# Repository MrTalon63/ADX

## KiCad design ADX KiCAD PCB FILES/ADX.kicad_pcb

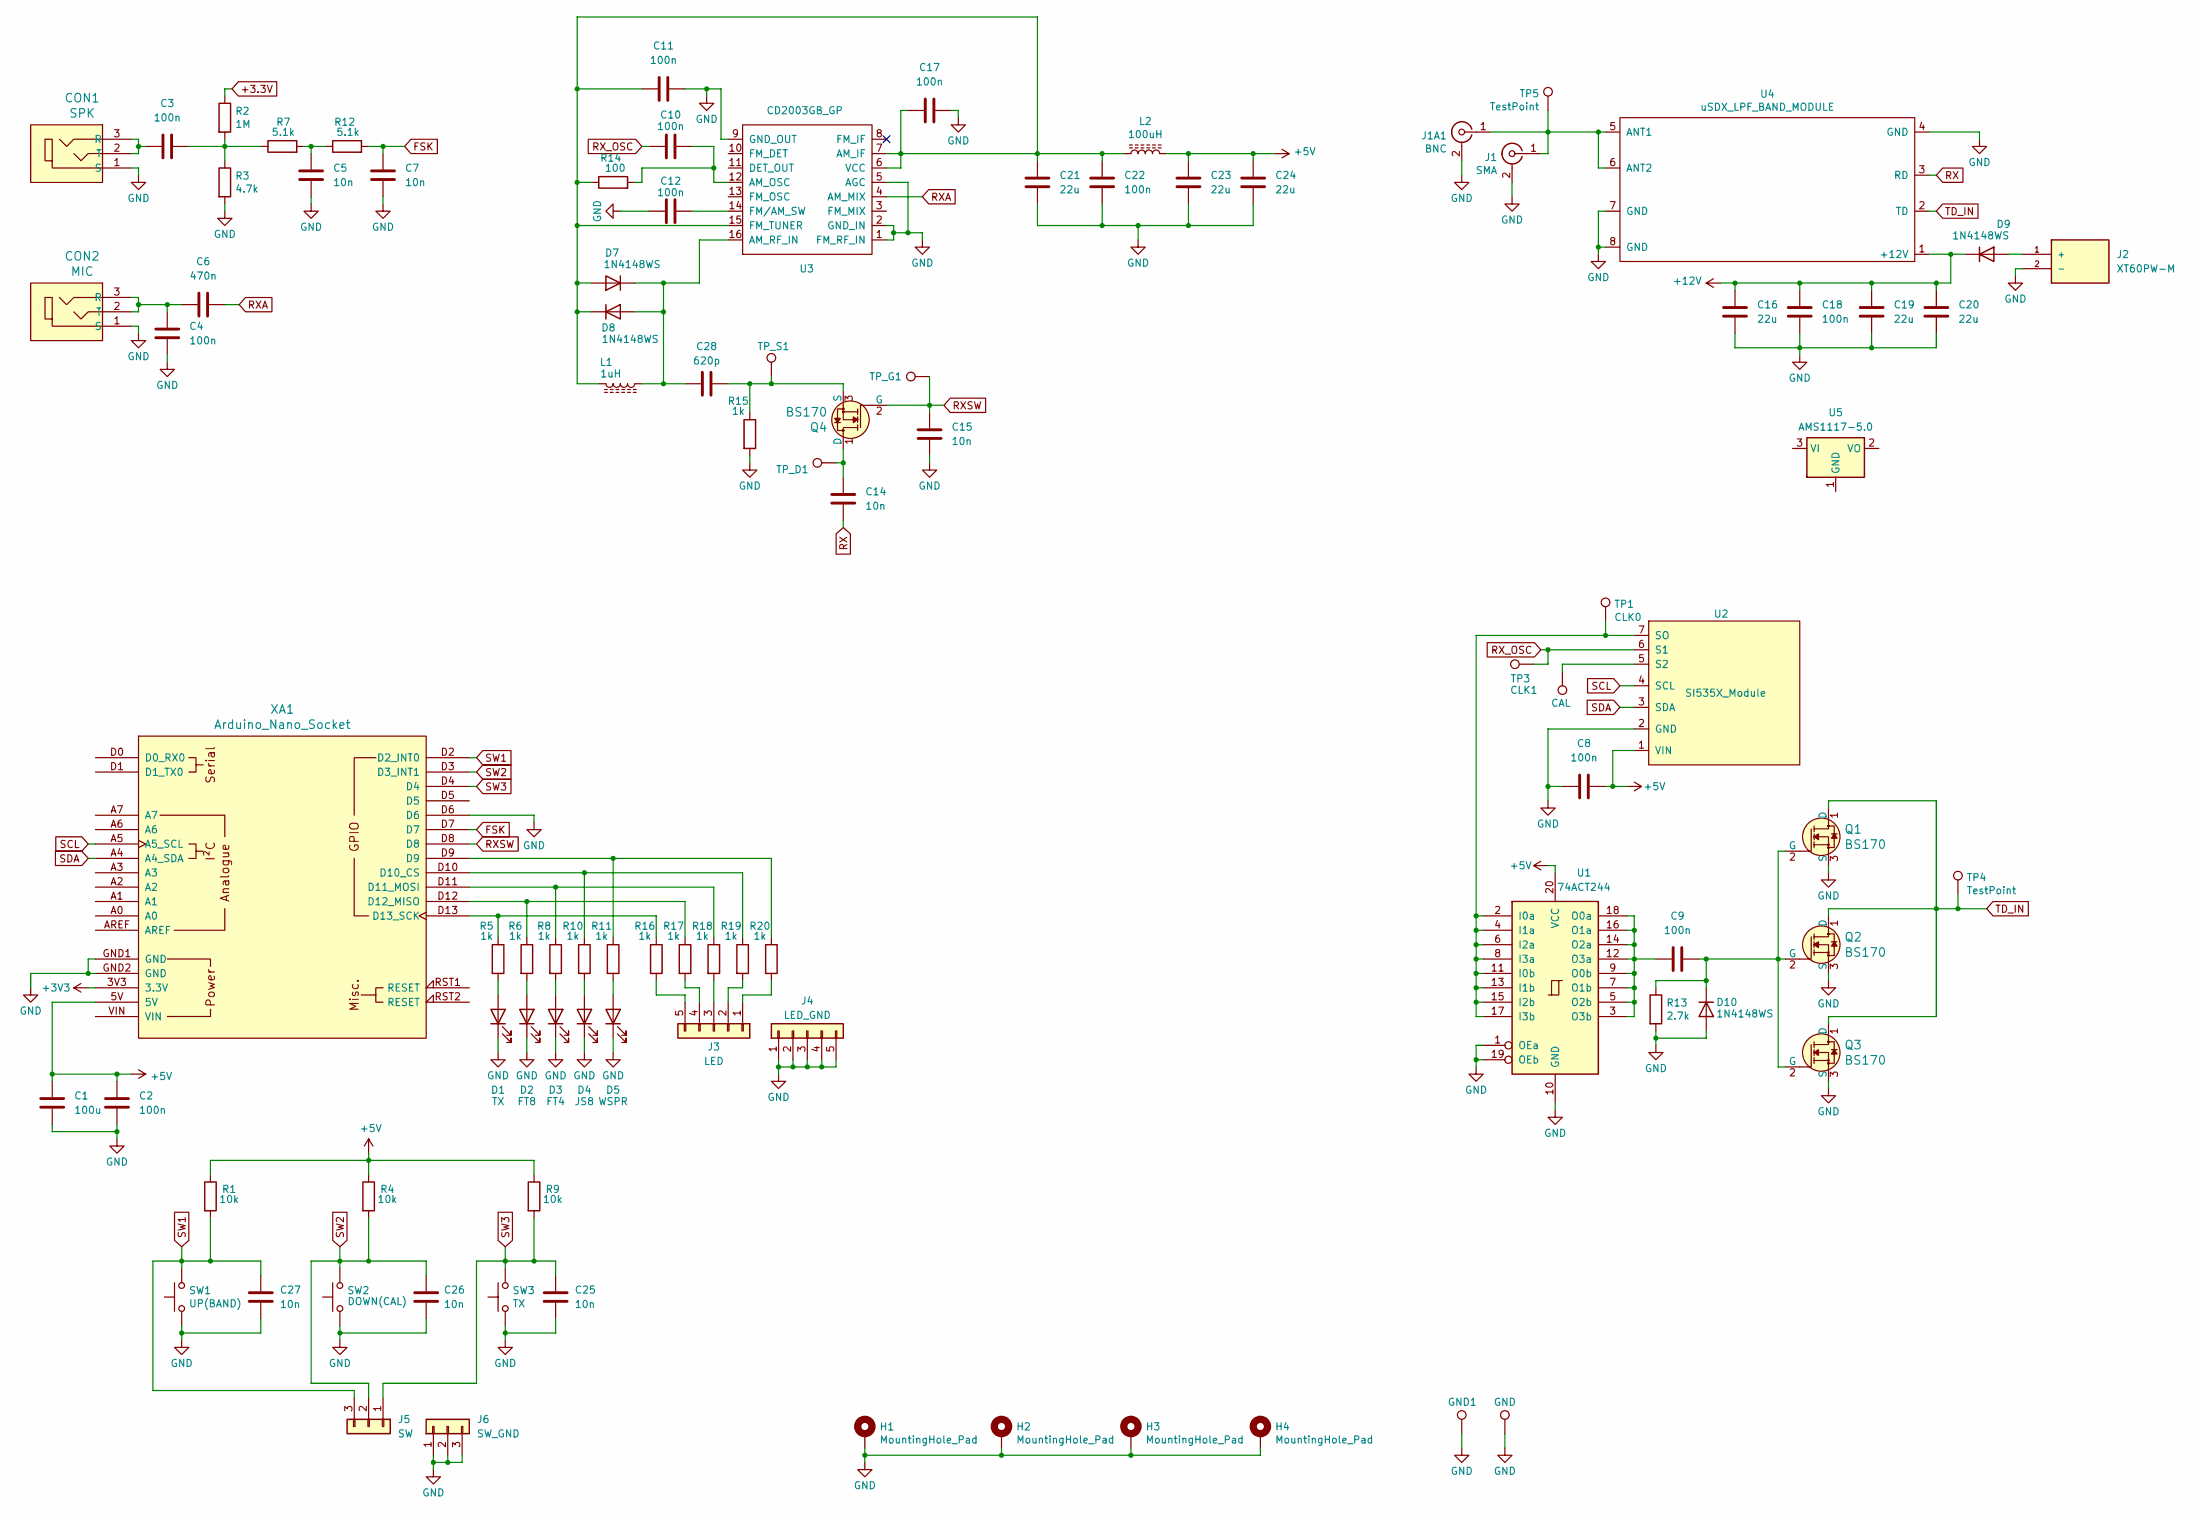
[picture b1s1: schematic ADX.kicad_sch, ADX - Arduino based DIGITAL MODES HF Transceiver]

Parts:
C1: 100u; C_1206_3216Metric
C2, C3, C4, C8, C9, C10, C11, C12, C17, C18, C22: 100n; C_0805_2012Metric
C5, C7, C14, C15, C25, C26, C27: 10n; C_0805_2012Metric
C6: 470n; C_0603_1608Metric
C16, C19, C20, C21, C23, C24: 22u; C_0805_2012Metric
C28: 620p; C_0805_2012Metric
CON1: SPK; Headphone_Jack_3.5mm_SJ1-3523N; MPN SJ1-3523N; Digi-Key_PN CP1-3523N-ND
CON2: MIC; Headphone_Jack_3.5mm_SJ1-3523N; MPN SJ1-3523N; Digi-Key_PN CP1-3523N-ND
D1: TX; LED_D3.0mm
D2: FT8; LED_D3.0mm
D3: FT4; LED_D3.0mm
D4: JS8; LED_D3.0mm
D5: WSPR; LED_D3.0mm
D7, D8, D9, D10: 1N4148WS; D_SOD-323
GND1: TestPoint_THTPad_2.0x2.0mm_Drill1.0mm
H1, H2, H3, H4: MountingHole_Pad; MountingHole_3.2mm_M3_ISO7380_Pad
J1: SMA; SMA_Samtec_SMA-J-P-X-ST-EM1_EdgeMount
J1A1: BNC; BNC_Amphenol_B6252HB-NPP3G-50_Horizontal
J2: XT60PW-M; AMASS_XT60PW-M; PARTREV V1.2
J3: LED; PinHeader_1x05_P2.54mm_Vertical
J4: LED_GND; PinHeader_1x05_P2.54mm_Vertical
J5: SW; PinHeader_1x03_P2.54mm_Vertical
J6: SW_GND; PinHeader_1x03_P2.54mm_Vertical
L1: 1uH; L_0805_2012Metric_Pad1.05x1.20mm_HandSolder
L2: 100uH; R_Axial_DIN0204_L3.6mm_D1.6mm_P2.54mm_Vertical
Q1, Q2, Q3: BS170; TO-92_HandSolder; MPN BS170; Digi-Key_PN BS170-ND
Q4: BS170; TO-92L_HandSolder; MPN BS170; Digi-Key_PN BS170-ND
R1, R4, R9: 10k; R_0402_1005Metric
R2: 1M; R_0402_1005Metric
R3: 4.7k; R_0402_1005Metric
R5, R6, R8, R10, R11, R15, R16, R17, R18, R19, R20: 1k; R_0402_1005Metric
R7, R12: 5.1k; R_0402_1005Metric
R13: 2.7k; R_0603_1608Metric
R14: 100; R_0402_1005Metric
SW1: UP(BAND); SW_PUSH_6mm
SW2: DOWN(CAL); SW_PUSH_6mm
SW3: TX; SW_PUSH_6mm
TP1: CLK0; TestPoint_THTPad_2.0x2.0mm_Drill1.0mm
TP2: CAL; TestPoint_THTPad_2.0x2.0mm_Drill1.0mm
TP3: CLK1; TestPoint_THTPad_2.0x2.0mm_Drill1.0mm
TP4, TP5: TestPoint; TestPoint_THTPad_2.0x2.0mm_Drill1.0mm
TP6: GND; TestPoint_THTPad_2.0x2.0mm_Drill1.0mm
TP_D1: TestPoint_THTPad_1.0x1.0mm_Drill0.5mm
TP_G1: TestPoint_THTPad_1.0x1.0mm_Drill0.5mm
TP_S1: TestPoint_THTPad_1.0x1.0mm_Drill0.5mm
U1: 74ACT244; TSSOP-20_4.4x6.5mm_P0.65mm
U2: SI535X_Module; SI5351 Module_Vertical
U3: CD2003GB_GP; DIP-16_W7.62mm_Socket_LongPads
U4: uSDX_LPF_BAND_MODULE; uSDX_LPF_Band_Module
U5: AMS1117-5.0; SOT-223-3_TabPin2
XA1: Arduino_Nano_Socket

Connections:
+3.3V: R2.1
+3V3: XA1.3V3 (3.3V)
+5V: C1.1, C2.1, C8.2, C23.1, C24.1, L2.1, R1.1, R4.1, R9.1, U1.20 (VCC), U2.1 (VIN), XA1.5V
+12V: C16.1, C18.1, C19.1, C20.1, D9.1 (K), U4.1 (+12V)
FSK: C7.2, R12.2, XA1.D7
GND: C1.2, C2.2, C4.1, C5.1, C7.1, C8.1, C11.2, C12.1, C15.1, C16.2, C17.2, C18.2, C19.2, C20.2, C21.2, C22.2, C23.2, C24.2, C25.1, C26.1, C27.1, CON1.1 (S), CON2.1 (S), D1.1 (K), D2.1 (K), D3.1 (K), D4.1 (K), D5.1 (K), D10.2 (A), GND1.1, H1.1, H2.1, H3.1, H4.1, J1.2 (Ext), J1A1.2 (Ext), J2.2 (-), J4.1, J4.2, J4.3, J4.4, J4.5, J6.1, J6.2, J6.3, Q1.3 (S), Q2.3 (S), Q3.3 (S), R3.2, R13.2, R15.2, SW1.1, SW2.1, SW3.1, TP6.1, U1.1 (OEa), U1.10 (GND), U1.19 (OEb), U2.2 (GND), U3.1 (FM_RF_IN), U3.2 (GND_IN), U3.5 (AGC), U3.9 (GND_OUT), U4.4 (GND), U4.7 (GND), U4.8 (GND), XA1.D6, XA1.GND1 (GND), XA1.GND2 (GND)
unnamed: C3.2, R2.2, R3.1, R7.1
unnamed: C5.2, R7.2, R12.1
unnamed: C3.1, CON1.2 (T), CON1.3 (R)
unnamed: C4.2, C6.1, CON2.2 (T), CON2.3 (R)
unnamed: D1.2 (A), R5.2
unnamed: D2.2 (A), R6.2
unnamed: D3.2 (A), R8.2
unnamed: D4.2 (A), R10.2
unnamed: D5.2 (A), R11.2
unnamed: C11.1, C17.1, C21.1, C22.1, D7.2 (A), D8.1 (K), L1.2, L2.2, R14.1, U3.6 (VCC), U3.7 (AM_IF), U3.15 (FM_TUNER)
unnamed: C28.2, D7.1 (K), D8.2 (A), L1.1, U3.16 (AM_RF_IN)
unnamed: D9.2 (A), J2.1 (+)
unnamed: C9.2, D10.1 (K), Q1.2 (G), Q2.2 (G), Q3.2 (G), R13.1
unnamed: J1.1 (In), J1A1.1 (In), TP5.1, U4.5 (ANT1), U4.6 (ANT2)
unnamed 20: J3.1, R20.2; also elsewhere on the board
unnamed 21: J3.2, R19.2; also elsewhere on the board
unnamed 22: J3.3, R18.2; also elsewhere on the board
unnamed 23: J3.4, R17.2; also elsewhere on the board
unnamed 24: J3.5, R16.2; also elsewhere on the board
unnamed: C14.2, Q4.1 (D), TP_D1.1
unnamed: C28.1, Q4.3 (S), R15.1, TP_S1.1
unnamed 27: R11.1, R20.1, XA1.D9; also elsewhere on the board
unnamed: TP1.1, U1.2 (I0a), U1.4 (I1a), U1.6 (I2a), U1.8 (I3a), U1.11 (I0b), U1.13 (I1b), U1.15 (I2b), U1.17 (I3b), U2.7 (SO)
unnamed: C9.1, U1.3 (O3b), U1.5 (O2b), U1.7 (O1b), U1.9 (O0b), U1.12 (O3a), U1.14 (O2a), U1.16 (O1a), U1.18 (O0a)
unnamed: TP2.1, U2.5 (S2)
unnamed: C10.2, R14.2, U3.12 (AM_OSC)
unnamed: C12.2, U3.14 (FM/AM_SW)
unnamed 33: R10.1, R19.1, XA1.D10 (D10_CS); also elsewhere on the board
unnamed 34: R8.1, R18.1, XA1.D11 (D11_MOSI); also elsewhere on the board
unnamed 35: R6.1, R17.1, XA1.D12 (D12_MISO); also elsewhere on the board
unnamed 36: R5.1, R16.1, XA1.D13 (D13_SCK); also elsewhere on the board
RX: C14.1, U4.3 (RD)
RXA: C6.2, U3.4 (AM_MIX)
RXSW: C15.2, Q4.2 (G), TP_G1.1, XA1.D8
RX_OSC: C10.1, TP3.1, U2.6 (S1)
SCL: U2.4 (SCL), XA1.A5 (A5_SCL)
SDA: U2.3 (SDA), XA1.A4 (A4_SDA)
SW1: C27.2, J5.3, R1.2, SW1.2, XA1.D2 (D2_INT0)
SW2: C26.2, J5.2, R4.2, SW2.2, XA1.D3 (D3_INT1)
SW3: C25.2, J5.1, R9.2, SW3.2, XA1.D4
TD_IN: Q1.1 (D), Q2.1 (D), Q3.1 (D), TP4.1, U4.2 (TD)

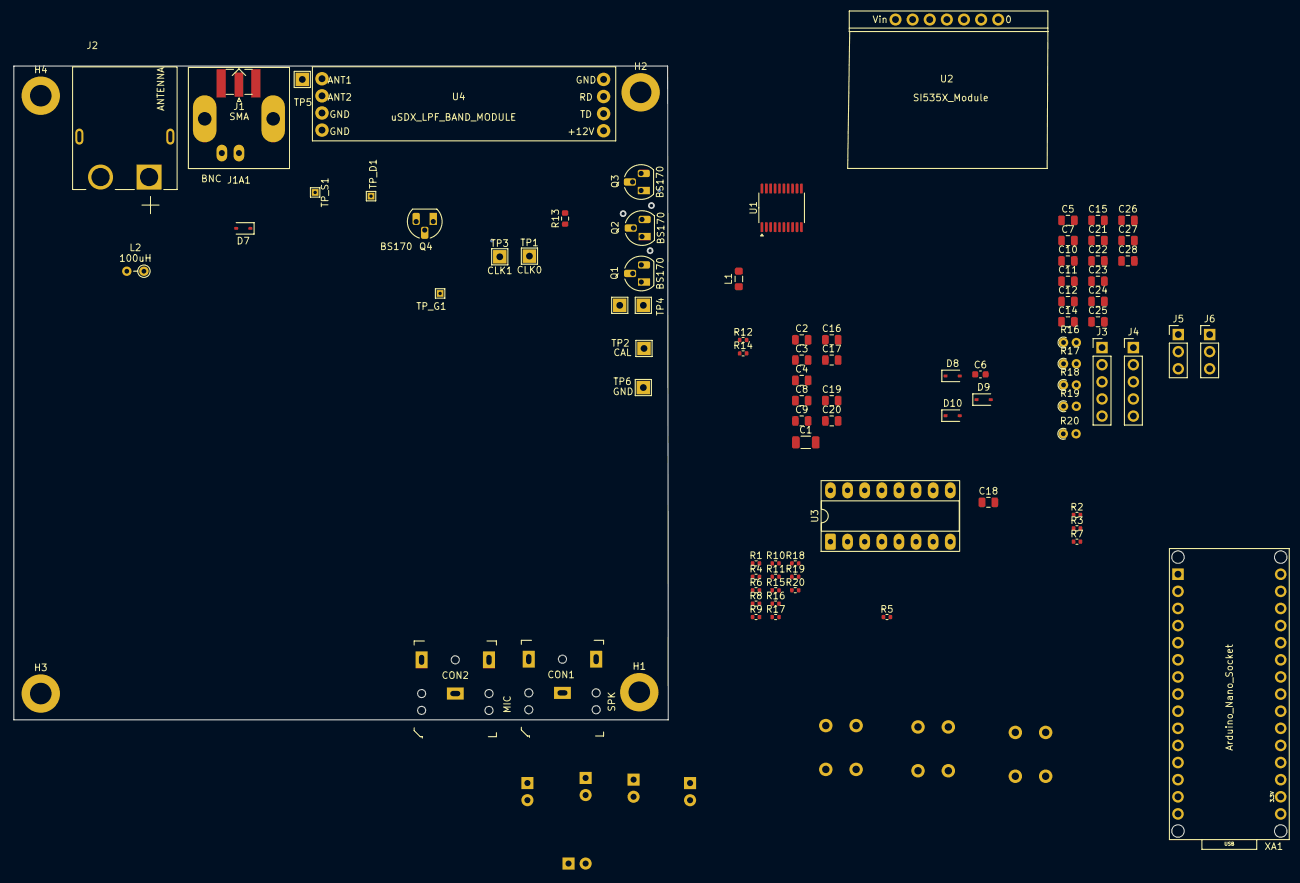
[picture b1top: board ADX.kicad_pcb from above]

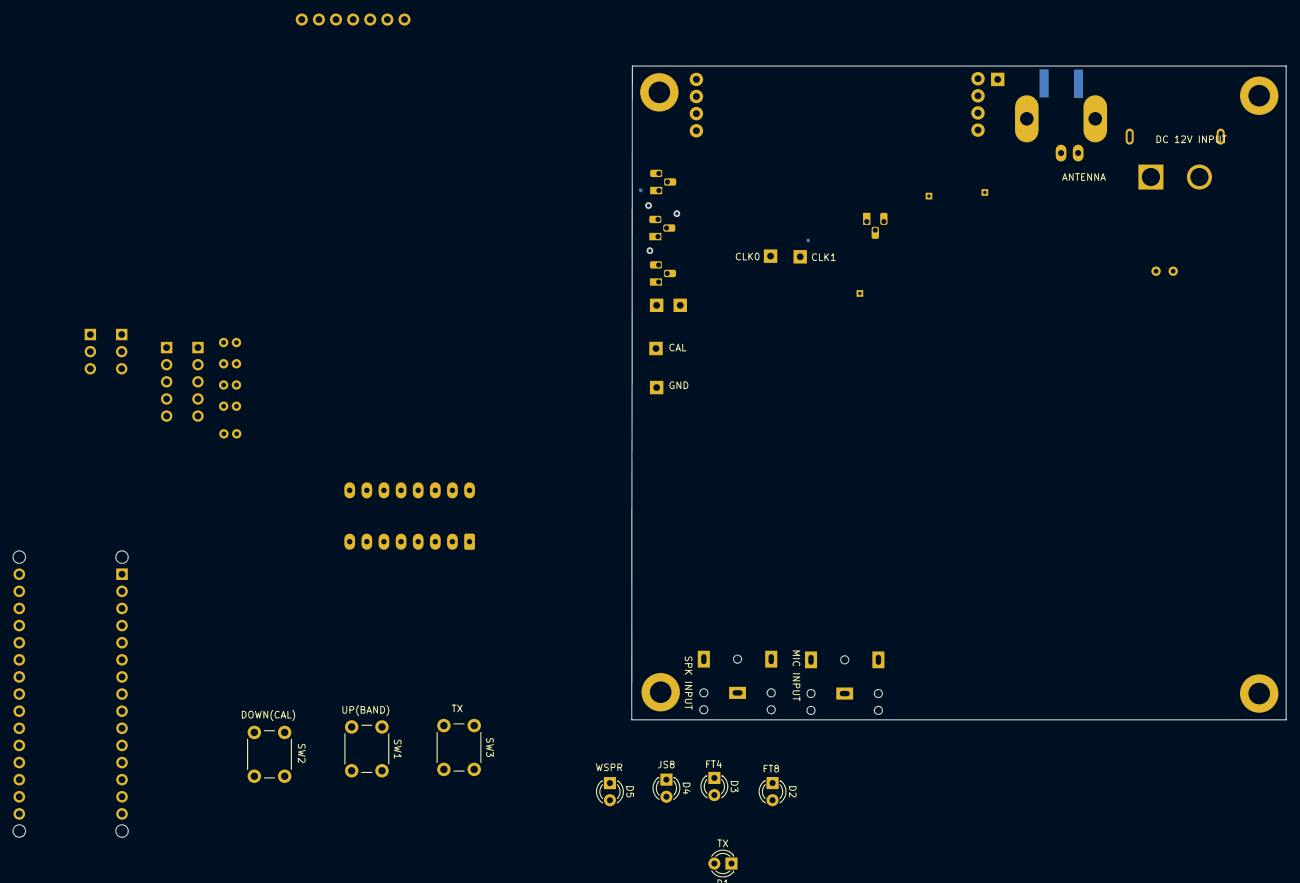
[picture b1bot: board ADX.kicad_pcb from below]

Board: 2 copper layers, 97.1 x 97.0 mm, 98 parts (8 on the bottom side), 45 nets.

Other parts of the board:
R16#2, R17#2: 1k; R_Axial_DIN0204_L3.6mm_D1.6mm_P1.90mm_Vertical
R18#2, R19#2, R20#2: 1k; R_0402_1005Metric

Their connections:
unnamed 20: R20#2.2; also elsewhere on the board
unnamed 21: R19#2.2; also elsewhere on the board
unnamed 22: R18#2.2; also elsewhere on the board
unnamed 23: R17#2.2; also elsewhere on the board
unnamed 24: R16#2.2; also elsewhere on the board
unnamed 27: R20#2.1; also elsewhere on the board
unnamed 33: R19#2.1; also elsewhere on the board
unnamed 34: R18#2.1; also elsewhere on the board
unnamed 35: R17#2.1; also elsewhere on the board
unnamed 36: R16#2.1; also elsewhere on the board

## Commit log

2025-04-16 Refactor
